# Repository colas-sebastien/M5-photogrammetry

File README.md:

# M5 Photogrammetry Project
_Hardware and Software to do low cost photogrammetry_

## Introduction

Based on the following project [Arduino controlled photogrammetry 3D-scanner](https://www.thingiverse.com/thing:3958326) I decided to replace the arduino by any device I2C compatible. (for the moment M5Stack devices)

Here are the different parts of the project:
- 3D scanner updated to replace the arduino by an electronic card control thanks to I2C with a Grovre connector
- An electronic card to control the 3D-scanner. The card will be control by I2C and will control the stepper motor. The card is also able to control a camera thanks to a micro jack
- M5Stack arduino code to control the electronic card and take photos thanks to mobile phone (thanks to BlueTooth) or Flucard for Pentax (Thanks to Wifi)

# Hardware: 3D Scanner

# Hardware: Electronic card

# Software: Arduino code for M5Stack

# Software: Arduino code for M5StickC
TODO

# Photo shooting

# Photogrammetry Software
Thanks to the previous steps we can have multiple photos of different angles of the object we want to reconstruct. It is now time to reconstruct the 3D Model.

Multiple Photogrammetry are available:
- [VisualSFM](http://ccwu.me/vsfm/)
- [MeshRoom](https://github.com/alicevision/meshroom/)
- [Regard3D](https://sourceforge.net/projects/regard3d/files/Regard3D/)

## VisualSFM
I created an installation script to Install [VisualSFM on Ubuntu 24.04](https://github.com/colas-sebastien/VisualSFM)

# Meshing Software

## MeshLab

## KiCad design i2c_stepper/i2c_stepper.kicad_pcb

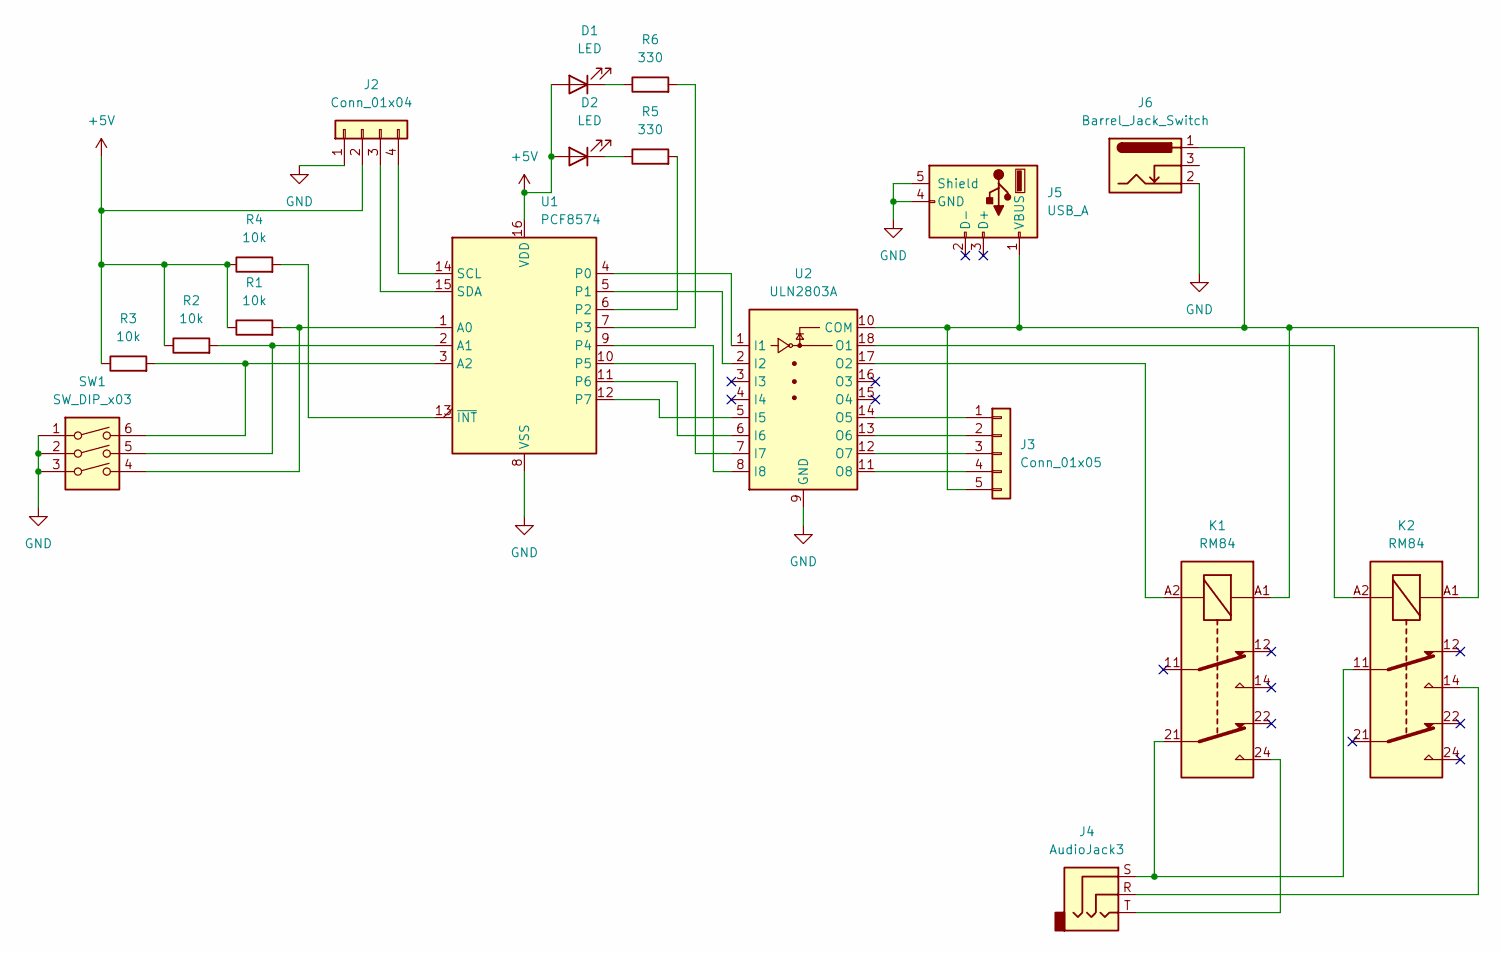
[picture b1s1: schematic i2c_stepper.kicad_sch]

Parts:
D1, D2: LED; LED_D5.0mm
J2: Conn_01x04; NS-Tech_Grove_1x04_P2mm_Vertical
J3: Conn_01x05; PinHeader_1x05_P2.54mm_Vertical
J4: AudioJack3; Jack_3.5mm_Ledino_KB3SPRS_Horizontal
J5: USB_A; USB_A_Stewart_SS-52100-001_Horizontal
J6: Barrel_Jack_Switch; BarrelJack_GCT_DCJ200-10-A_Horizontal
K1, K2: RM84; Relay_DPDT_Finder_30.22
R1, R2, R3, R4: 10k; R_Axial_DIN0411_L9.9mm_D3.6mm_P15.24mm_Horizontal
R5, R6: 330; R_Axial_DIN0411_L9.9mm_D3.6mm_P15.24mm_Horizontal
SW1: SW_DIP_x03; SW_DIP_SPSTx03_Slide_9.78x9.8mm_W7.62mm_P2.54mm
U1: PCF8574; DIP-16_W7.62mm_Socket
U2: ULN2803A; DIP-18_W7.62mm_Socket

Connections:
+5V: D1.2 (A), D2.2 (A), J2.2, R1.1, R2.1, R3.1, R4.1, U1.16 (VDD)
GND: J2.1, J5.4 (GND), J5.5 (Shield), J6.2, SW1.1, SW1.2, SW1.3, U1.8 (VSS), U2.9 (GND)
unnamed: D1.1 (K), R6.1
unnamed: D2.1 (K), R5.1
unnamed: J2.3, U1.15 (SDA)
unnamed: J2.4, U1.14 (SCL)
unnamed: J3.1, U2.14 (O5)
unnamed: J3.2, U2.13 (O6)
unnamed: J3.3, U2.12 (O7)
unnamed: J3.4, U2.11 (O8)
unnamed: J3.5, J5.1 (VBUS), J6.1, K1.A1, K2.A1, U2.10 (COM)
unnamed: J4.R, K2.14
unnamed: J4.S, K1.21, K2.11
unnamed: J4.T, K1.24
unnamed: R1.2, SW1.4, U1.1 (A0)
unnamed: R2.2, SW1.5, U1.2 (A1)
unnamed: R3.2, SW1.6, U1.3 (A2)
unnamed: U1.4 (P0), U2.1 (I1)
unnamed: U1.5 (P1), U2.2 (I2)
unnamed: R5.2, U1.6 (P2)
unnamed: R6.2, U1.7 (P3)
unnamed: U1.9 (P4), U2.8 (I8)
unnamed: U1.10 (P5), U2.7 (I7)
unnamed: U1.11 (P6), U2.6 (I6)
unnamed: U1.12 (P7), U2.5 (I5)
unnamed: R4.2, U1.13 (~INT)
unnamed: K2.A2, U2.18 (O1)
unnamed: K1.A2, U2.17 (O2)

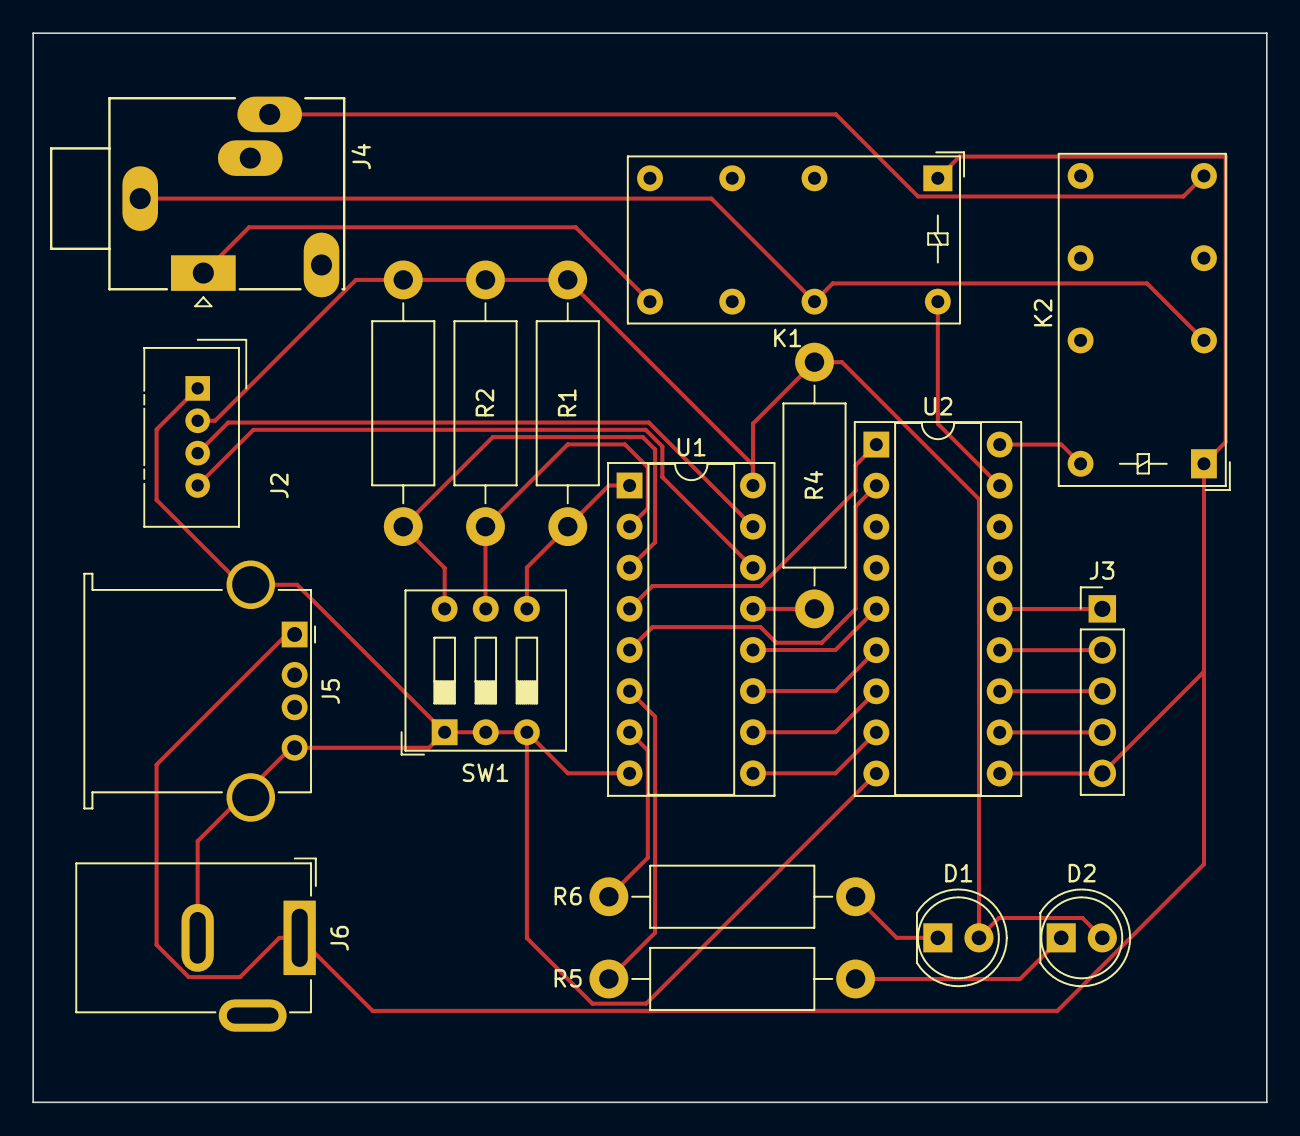
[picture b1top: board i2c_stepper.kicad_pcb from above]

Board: 2 copper layers, 76.2 x 66.0 mm, 18 parts (0 on the bottom side), 28 nets.

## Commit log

2024-10-02 M5Stack code + PCB extension card + 3D Model
2024-10-02 Readme updated
2024-10-06 current photo number modification
2024-10-17 More photos on documentation
2024-12-26 documentation update
